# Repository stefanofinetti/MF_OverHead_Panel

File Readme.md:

# Overhead Panel

A compact Airbus A319/320/321 overhead panel for MobiFlight: 3D-printed
panels and Korry-style push buttons, the boards that carry every switch,
light and display, and the firmware for its three OLED displays.

The panel covers **ADIRS**, **AIR COND**, **ANTI ICE**, **APU**, **ELEC**,
**EXT LT**, **FUEL**, **GPWS** and **SIGNS**.

## v2 in short

v1 is one four-layer board, 313 × 206 mm, behind the whole panel. It works,
but it costs well over €100 once shipping and customs are added, and a
single mistake means reordering all of it.

v2 follows the printed panels instead: **eight small section boards, one
under each panel, and a 137 × 89 mm mainboard on the floor of the case**,
joined by ribbon cables. All nine are two-layer, 1.6 mm boards.

* **The printed parts do not change.** Panels, frames, Korry buttons and
  cases are the same. Only the floor of the lower-left case part is
  reprinted, with four bosses for the mainboard.
* **The section boards are cut out of the v1 layout.** Every switch, LED
  and hole stays at its v1 position, so each panel screws down exactly as
  before.
* **The pin map does not change.** Every switch is on the same ATmega pin
  and every annunciator on the same bit of the same shift-register chain,
  so the module config and the MobiFlight project stay valid. A few
  additions are listed under [Moving from v1](#moving-from-v1).

**Status (September 2026):** all nine boards are drawn and routed. ERC,
DRC and schematic parity are clean, and every ribbon and backlight pin was
checked against the board at the other end. **Nothing has been ordered or
built yet.** The firmware v2 needs is in `SF_OVHD` 1.2.0. The reprinted
case floor is still to do. v1 is the board that has been built and tested. It is
kept in `Kicad Files/` as the reference the v2 boards were cut from, **not
to be built**: build v2.

## What is in the repository

| Folder | What it holds |
|---|---|
| `Mainboard/` | The v2 mainboard: KiCad project, schematic (a root sheet and six sub-sheets) and routed PCB. See [its readme](Mainboard/README.md) |
| `Section_ADIRS/` … `Section_SIGNS/` | The eight v2 section boards, one KiCad project each, with a readme apiece |
| `Libraries/` | Parts shared by every v2 board: `OVHD.pretty` (Korry, toggle, ADR rotary, annunciator LED), `OVHD.kicad_sym`, and `3dmodels/` |
| `docs/board-split.md` | The v2 design document: decisions, power, annunciator currents, the ribbon pinouts, and why each choice was made |
| `SF_OVHD/` | The MobiFlight firmware and the installable Community package, with the module config for the panel. See [its readme](SF_OVHD/README.md) |
| `STL Files/` | Everything to print: one STL per filament colour for each panel, a ready `.3mf` for multi-colour printers, the Korry buttons and cases, the four case parts, the frames and the support |
| `STL Files/FaceDown_Printing/` | The APU panel redesigned to print face down. The other panels will follow |
| `STL Files/Levers/` | The exterior light levers and the paddle knobs |
| `3D Files/` | The SketchUp sources for the panel, the Korry buttons and the support |
| `Kicad Files/` | **v1**, for reference only: the single big board, as sent to JLCPCB on 3 March 2025. Do not build it |

`OverheadPanel.zip` is an older snapshot of `Kicad Files/` from January
2025, kept for reference.

## The boards

```
                        ┌─ ribbon ──► 8 section boards (switches, annunciators, backlight LEDs)
 9 V jack ─► mainboard ─┤
 USB-B    ─►            └─ 2 wires ─► 8 section boards (backlight, 9 V)
```

The mainboard carries every active part. The section boards carry only
their switches, LEDs and resistors, and the OLED sockets.

| Board | PCB (mm) | Switches | Annunciators | Backlight LEDs | Ribbon → mainboard | Backlight → mainboard |
|---|---|---|---|---|---|---|
| [ADIRS](Section_ADIRS/README.md) | 132.5 × 81.5 | 3 ADR rotaries, GND CTL | 1 | 18 | 20 pins → J701 | J601 |
| [FUEL](Section_FUEL/README.md) | 177.5 × 40 | 7 Korry | 14 | 14 | 26 pins → J702 | J602 |
| [ELEC](Section_ELEC/README.md) | 177.5 × 39.5 | 3 Korry | 5 | 10 | 20 pins → J703 | J603 |
| [GPWS](Section_GPWS/README.md) | 159.5 × 39 | 4 Korry | 6 | 9 | 14 pins → J704 | J604 |
| [AIR COND](Section_AIRCOND/README.md) | 150.5 × 39 | 4 Korry | 8 | 13 | 16 pins → J705 | J605 |
| [EXT LT](Section_EXTLT/README.md) | 159.5 × 79.5 | 8 toggles | — | 31 | 14 pins → J706 | J606 |
| [APU](Section_APU/README.md) | 39 × 79.5 | 2 Korry | 4 | 5 | 10 pins → J707 | J607 |
| [SIGNS](Section_SIGNS/README.md) | 108.5 × 79.5 | 3 Korry, 3 toggles | 6 | 22 | 16 pins → J708 | J608 |
| **Total** | | **49 inputs** | **44** | **122** | | |

The three OLEDs (BATT 1, BATT 2 on ELEC, ADIRS on ADIRS) plug into sockets
on their section boards, as on v1, and reach the mainboard through the
ribbon.

### The mainboard

137 × 89 mm, two layers, GND poured on both. The chips and connectors are on
top, and the small 1206 parts of the dense groups are underneath their chip.

* **Microcontroller:** ATmega2560 with a CH340G for USB. MobiFlight sees it
  as a Mega.
* **Power:** 9 V in through reverse protection, a TVS and a 470 µF bulk
  capacitor, then two resettable fuses, one for the backlight and one for
  the MIC29302 5 V regulator. A TPS2115A feeds the logic from that 5 V, or
  from USB when the 9 V is off. An AMS1117 makes 3.3 V for the PCA9548A
  and the OLEDs.
* **Annunciators:** four TI TLC5927 constant-current sinks, one per legend
  colour, in the two v1 chains (`ANN_LOWER`, `ANN_UPPER`). Each has a fixed
  1 kΩ on `R-EXT`, about 19 mA per LED. The trimmers of v1 are gone.
* **Three switches driven by the firmware:**
  * **D44:** backlight dimmer, an IRLIZ44N on the common return of the
    eight backlight branches;
  * **D45:** annunciator dimmer, on the LED anode rail;
  * **D46:** power to the four TLC5927, so they start clean however the
    9 V was plugged in.

  D44 and D45 undriven means dark.
* **Displays:** a PCA9548A I2C multiplexer at 0x71, channels 0–2 for
  BATT 1, BATT 2 and ADIRS.

### The section boards

* Every v1 part stays at its v1 coordinates. The new parts go on the
  **back**: the shrouded IDC header, the JST PH backlight connector and the
  few new resistors. Nothing new stands proud of the front.
* No ICs. The annunciator LEDs have no resistors, because the TLC5927 is a
  current sink.
* Backlight strings of two LEDs on 150 Ω, at 17 mA. Where the split leaves
  one LED alone (GPWS, AIR COND, EXT LT, APU), it gets 330 Ω for the same
  current.
* Each board sits in the middle of its A4 sheet. Its grid origin is set to
  where v1's (0, 0) lies, so KiCad shows v1 coordinates. The offset is in
  the title block.

## Building one

1. **Print** the panels, buttons, cases and frames from `STL Files/`.
2. **Reprint the floor of the lower-left case part** with four bosses and M3
   heat-set inserts for the mainboard. The mainboard's M3 holes are 4 mm in
   from its corners. The floor is free over 141 × 93.5 mm between the
   pillars. The reprinted floor is not drawn yet.
3. **Order the boards.** Run the Fabrication Toolkit plugin in each of the
   nine projects to make the Gerbers, BOM and positions. No v2 production
   files have been generated yet.
4. **Assemble.** Everything is sized for hand soldering: 1206 passives,
   7 × 5 mm crystals, generous spacing. Values, polarity, pin 1 and `K`
   marks are on the silkscreen of the side each part is on, so no
   schematic is needed at the bench. The per-board readmes list what to
   watch for.
5. **Cable it:**
   * one straight IDC ribbon per board, pin 1 to pin 1, from J1 on the
     section board to its J70x;
   * one pair of 22–24 AWG wires per board, from J2 (JST PH, `+` and `−` on
     the silkscreen) to its J60x screw terminal, pin 1 `+`;
   * the 9 V from a panel-mount 5.5 × 2.1 jack to J101 (pin 1 `+`);
   * USB through a panel-mount USB-B extension to P201.
6. **Burn the bootloader.** A new ATmega2560 is blank. J201 is an in-line
   ISP header: 1 VCC, 2 RESET, 3 MISO, 4 MOSI, 5 SCK, 6 GND. With JP201 on
   2–3, the programmer powers the MCU alone. Burn the Arduino Mega
   bootloader once, then put JP201 back on 1–2. From then on, the board is
   flashed over USB like a Mega.
7. **Install the firmware and the module config**, as described in
   [the firmware readme](SF_OVHD/README.md), then bind the switches and
   lights in your MobiFlight project.

A 9 V / 3 A adapter is enough. The backlight takes about 1.1 A, and a light
test with all 44 annunciators lit adds about 1 A.

## Moving from v1

The pin map is the same, so the v1 module config and project keep working,
with these changes:

* **Flash `SF_OVHD` 1.2.0 or later.** Its custom device powers the TLC5927
  up through D46 once the board has started. With older or stock MobiFlight
  firmware the annunciators stay dark on v2.
* **Load the module config from the 1.2.0 package.** It adds two PWM outputs,
  `BL_PWM` on D44 (backlight) and `ANN_PWM` on D45 (annunciators). D46 is not
  in it, because the custom device owns it.
* **Two new rows in the MobiFlight project** to drive them, typically INTEG
  LT for D44 and ANN LT BRT/DIM for D45. At 0, or with the Connector
  closed, the backlight and the annunciators are dark.
* **NO SMOKING:** v1 read it on the toggle's other contact, and the
  MobiFlight row was inverted to make up for it. v2 reads it like every
  other toggle, so **remove the inversion** on that row.

## Known issues

* **The ADIRS panel labels its rotaries in the wrong order.** The printed
  panel reads ADR 1, ADR 2, ADR 3 from left to right. On the A320 the order
  is IR 1, IR 3, IR 2, and that is how the board is wired, on v1 and v2
  alike: the middle rotary is IR 3 and the right one is IR 2. The `.mfmc`
  follows the board. Only the printed labels are wrong, so read the middle
  knob as 3 and the right one as 2 until the panel is reprinted.

## Software

* [KiCad](https://www.kicad.org/) 10, for the v2 boards. The files are
  saved by KiCad 10 and do not open in older versions
* [Freerouting](https://github.com/freerouting/freerouting), only to
  reroute a board
* [SketchUp](https://www.sketchup.com), to change the printed parts
* [VS Code](https://code.visualstudio.com/) with
  [PlatformIO](https://platformio.org/), to build the firmware
* [MobiFlight](https://www.mobiflight.com/)

```bash
git clone https://github.com/stefanofinetti/MF_OverHead_Panel.git
```

## License

This code and all the items are released under the GPLv3.0 license. Feel free
to use them as you wish, as long as you redistribute the source code.
A mention would be nice, though, if you use this work: I invested a good
many hours in it, just for the amazing MobiFlight community.

## Acknowledgements

This project couldn't have seen the light without the excellent work, and
kind support, of [GaGagu](https://github.com/gagagu) and
[ElRal](https://github.com/elral). Their work is amazing, so please have a
look at their repositories.

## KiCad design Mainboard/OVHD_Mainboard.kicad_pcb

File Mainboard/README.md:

# OVHD Mainboard (v2)

The v2 mainboard: the microcontroller, power, annunciator drivers and
display multiplexer for the whole overhead. It sits on the floor of the
lower-left case part and reaches the eight section boards through ribbons
and backlight wires. The reasoning behind every choice is in
[`docs/board-split.md`](../docs/board-split.md).

* **PCB:** 137 × 89 mm, 2 layers, 1.6 mm, GND poured on both sides.
* **Fixing:** four M3 holes, 4 mm in from the corners, for bosses with
  heat-set inserts in the reprinted case floor.
* **Parts:** 123. 65 of them are on the bottom.
* **Status:** routed with Freerouting. ERC, DRC (every warning on) and
  schematic parity are clean. Not yet ordered.

**Top**, with the chips and connectors:

**Bottom**, with the small 1206 parts under their chips:

Rendered by KiCad from the board file. The bottom is seen from below, so it
is mirrored against the top.

## Schematic

| Sheet | What is on it |
|---|---|
| `power.kicad_sch` | 9 V in, reverse diode, TVS, bulk capacitor, the two fuses, MIC29302 (5 V) |
| `usb_supply.kicad_sch` | USB-B, CH340G, TPS2115A supply selector, AMS1117 (3.3 V), ISP header, JP201 |
| `mcu.kicad_sch` | ATmega2560, 16 MHz crystal, reset, decoupling |
| `i2c.kicad_sch` | PCA9548A, address switch, pull-ups |
| `annunciators.kicad_sch` | The four TLC5927, the anode dimmer (D45) and the TLC5927 supply switch (D46) |
| `connectors.kicad_sch` | The eight ribbon headers, the eight backlight terminals, the backlight dimmer (D44) |

Local libraries: `TLC5927.kicad_sym` / `TLC5927.pretty` and
`TPS2115A.kicad_sym`. Every part has a description field that says why it
is there and, where it replaces a v1 part, which one.

## Connectors and settings

| Ref | What | Notes |
|---|---|---|
| J101 | 9 V in, 5.08 mm screw terminal | From the panel-mount 5.5 × 2.1 jack. Pin 1 `+` |
| P201 | USB-B | To the panel-mount USB-B extension |
| J201 | ISP header, 1 × 6 | 1 VCC, 2 RESET, 3 MISO, 4 MOSI, 5 SCK, 6 GND |
| JP201 | Power selector | 1–2: MCU from the board's 5 V (normal use). 2–3: MCU from J201's VCC only, to burn the bootloader |
| SW401 | PCA9548A address | All off = 0x70. **Set A0 on: the board runs at 0x71**, which `SF_OVHD` expects |
| J701–J708 | Ribbons to ADIRS, FUEL, ELEC, GPWS, AIR COND, EXT LT, APU, SIGNS | Shrouded, keyed. Straight ribbon, pin 1 to pin 1. Each is labelled on the silkscreen with its board |
| J601–J608 | Backlight to the same eight boards, in the same order | 3.5 mm screw terminals. Pin 1 `+9V_BL`, pin 2 the switched return |

The pinout of every ribbon is in the design document, under *Ribbon
pinouts*.

## Annunciator drivers

| Ref | Colour | Chain and bits | v1 ref |
|---|---|---|---|
| U501 | white | `ANN_LOWER` 0–15 | U6 |
| U502 | blue | `ANN_LOWER` 16–31 | U7 |
| U503 | amber | `ANN_UPPER` 0–15 | U8 |
| U504 | green and amber | `ANN_UPPER` 16–31 | U5 |

`ANN_LOWER` has its latch on D23, clock on D24 and data on D22. `ANN_UPPER`
has its latch on D27, clock on D26 and data on D25, as on v1.

* **`R-EXT` is a fixed 1 kΩ (R501–R504):** I = 1.25 V / R × 15 ≈ 19 mA
  per LED. If you ever change it, stay between ~160 Ω and ~1.9 kΩ, the
  chip's range at power-up.
* **Nothing else on `R-EXT`,** above all no capacitor. On the v1 board a
  100 nF there made the chips drop their outputs as soon as two or three
  were on together. See the design document.
* **`OE` is tied hard to GND.** On the TLC5927 it is also the mode pin, so
  it must never get PWM.
* **1 kΩ in series on CLK, LE and SDI (R511–R520),** at the chips' end.

## Pins the firmware drives

| Pin | Drives | Undriven or low |
|---|---|---|
| D44 | Q601 (IRLIZ44N), the common return of the backlight | backlight off |
| D45 | Q501/Q502, the annunciator anode rail `+5V_LED` | annunciators dark |
| D46 | Q503/Q504, the TLC5927 supply | TLC5927 unpowered |

D44 and D45 are plain MobiFlight PWM outputs, `BL_PWM` and `ANN_PWM` in the
`.mfmc`. D46 belongs to the `SF_OVHD` custom device, from firmware 1.2.0. It
powers the chips up after the board has started, and again on message 5. See
[the firmware readme](../SF_OVHD/README.md#annunciator-power-up-d46).

## Assembly notes

* **Bottom side:** the 1206 parts of the dense groups, each under its chip:
  * the MCU and CH340G decoupling and crystal parts;
  * the I2C pull-ups;
  * the TLC5927 `R-EXT` resistors, VDD capacitors and series resistors;
  * the resistors of the three MOSFET switches;
  * the MIC29302 feedback divider and capacitors.

  Solder the bottom side first, then the top.
* **Q601** lies flat on its isolated tab. At ~1.1 A it needs no heatsink.
* **The polarity marks are on the silkscreen:** the electrolytics, the `K` at D101
  and at the power LED D201, and `+` and `−` at J101 and at every
  backlight terminal. D102 (SMBJ12CA) is bidirectional: it fits either way round.
* **Before flashing any firmware,** burn the bootloader through
  J201 with JP201 on 2–3, then move JP201 back to 1–2.

## Design rules

| Net class | Track | Clearance | Nets |
|---|---|---|---|
| HiCurrent | 0.8 mm | 0.3 mm | `VIN_RAW`, `+9V`, `+9V_BL`, `BL_RET` |
| Power | 0.5 mm | 0.25 mm | `+9V_REG`, `+5V_LED` |
| PowerNarrow | 0.35 mm | 0.2 mm | `5V_EXT`, `VBUS`, the widest that enters the TPS2115A's 0.65 mm pins |
| Default | 0.25 mm | 0.2 mm | everything else |

The minimum track is 0.15 mm, for a few escapes between TQFP and SOIC pins,
within JLCPCB's 0.127 mm.

## Mechanical

* The board is drawn in v1 coordinates, at x 32–169, y 134.5–223.5, under
  EXT LT and the lower edge of GPWS. That way it can be checked against the
  section boards above it.
* EXT LT's J1 and J2 hang over the TLC5927 block, where nothing is taller
  than a SOIC. No ribbon header sits under another board's connector.
* With today's case there are 27 mm from the floor to the underside of the
  section boards. The reprinted floor is meant to raise that to 30–35 mm.

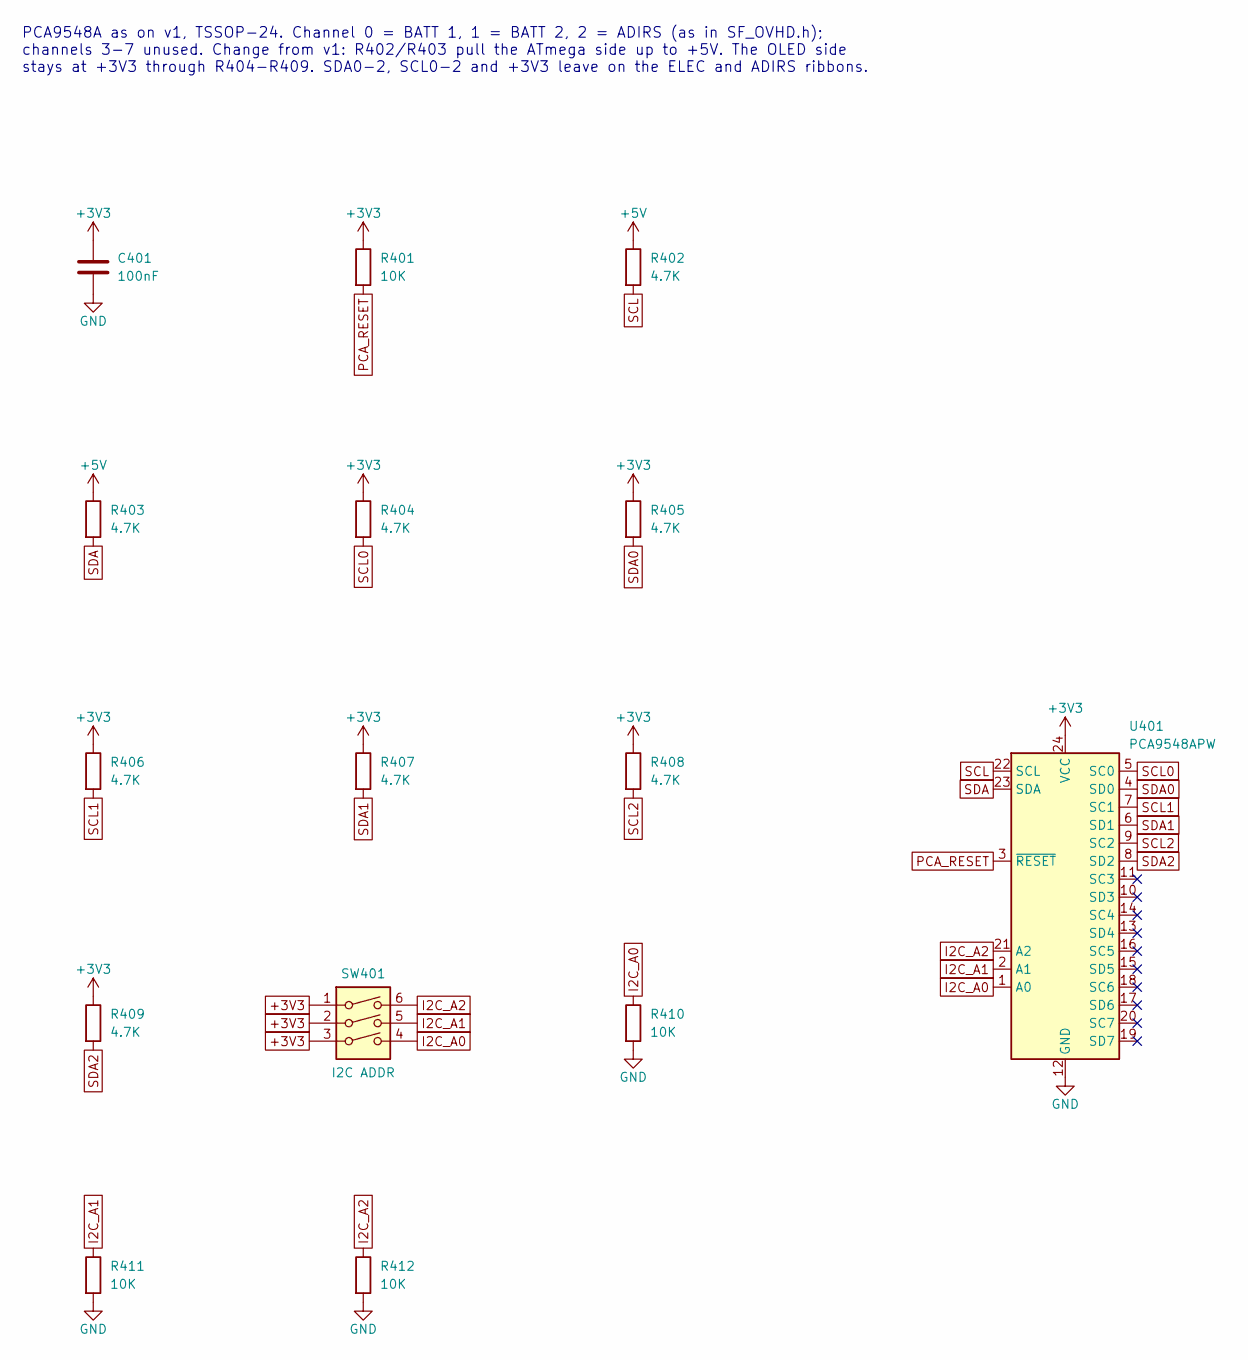
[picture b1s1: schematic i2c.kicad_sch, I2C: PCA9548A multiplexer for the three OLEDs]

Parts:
C401: 100nF; C_1206_3216Metric_Pad1.33x1.80mm_HandSolder
R401, R410, R411, R412: 10K; R_1206_3216Metric_Pad1.30x1.75mm_HandSolder
R402, R403, R404, R405, R406, R407, R408, R409: 4.7K; R_1206_3216Metric_Pad1.30x1.75mm_HandSolder
SW401: I2C ADDR; SW_DIP_SPSTx03_Slide_9.78x9.8mm_W7.62mm_P2.54mm
U401: PCA9548APW; TSSOP-24_4.4x7.8mm_P0.65mm

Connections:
+3V3: C401.1, R401.1, R404.1, R405.1, R406.1, R407.1, R408.1, R409.1, SW401.1, SW401.2, SW401.3, U401.24 (VCC); also elsewhere on the board
+5V: R402.1, R403.1; also elsewhere on the board
GND: C401.2, R410.2, R411.2, R412.2, U401.12 (GND); also elsewhere on the board
I2C_A0: R410.1, SW401.4, U401.1 (A0)
I2C_A1: R411.1, SW401.5, U401.2 (A1)
I2C_A2: R412.1, SW401.6, U401.21 (A2)
PCA_RESET: R401.2, U401.3 (~RESET)
SCL: R402.2, U401.22 (SCL); also elsewhere on the board
SCL0: R404.2, U401.5 (SC0); also elsewhere on the board
SCL1: R406.2, U401.7 (SC1); also elsewhere on the board
SCL2: R408.2, U401.9 (SC2); also elsewhere on the board
SDA: R403.2, U401.23 (SDA); also elsewhere on the board
SDA0: R405.2, U401.4 (SD0); also elsewhere on the board
SDA1: R407.2, U401.6 (SD1); also elsewhere on the board
SDA2: R409.2, U401.8 (SD2); also elsewhere on the board

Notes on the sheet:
PCA9548A as on v1, TSSOP-24. Channel 0 = BATT 1, 1 = BATT 2, 2 = ADIRS (as in SF_OVHD.h); channels 3-7 unused. Change from v1: R402/R403 pull the ATmega side up to +5V. The OLED side stays at +3V3 through R404-R409. SDA0-2, SCL0-2 and +3V3 leave on the ELEC and ADIRS ribbons.

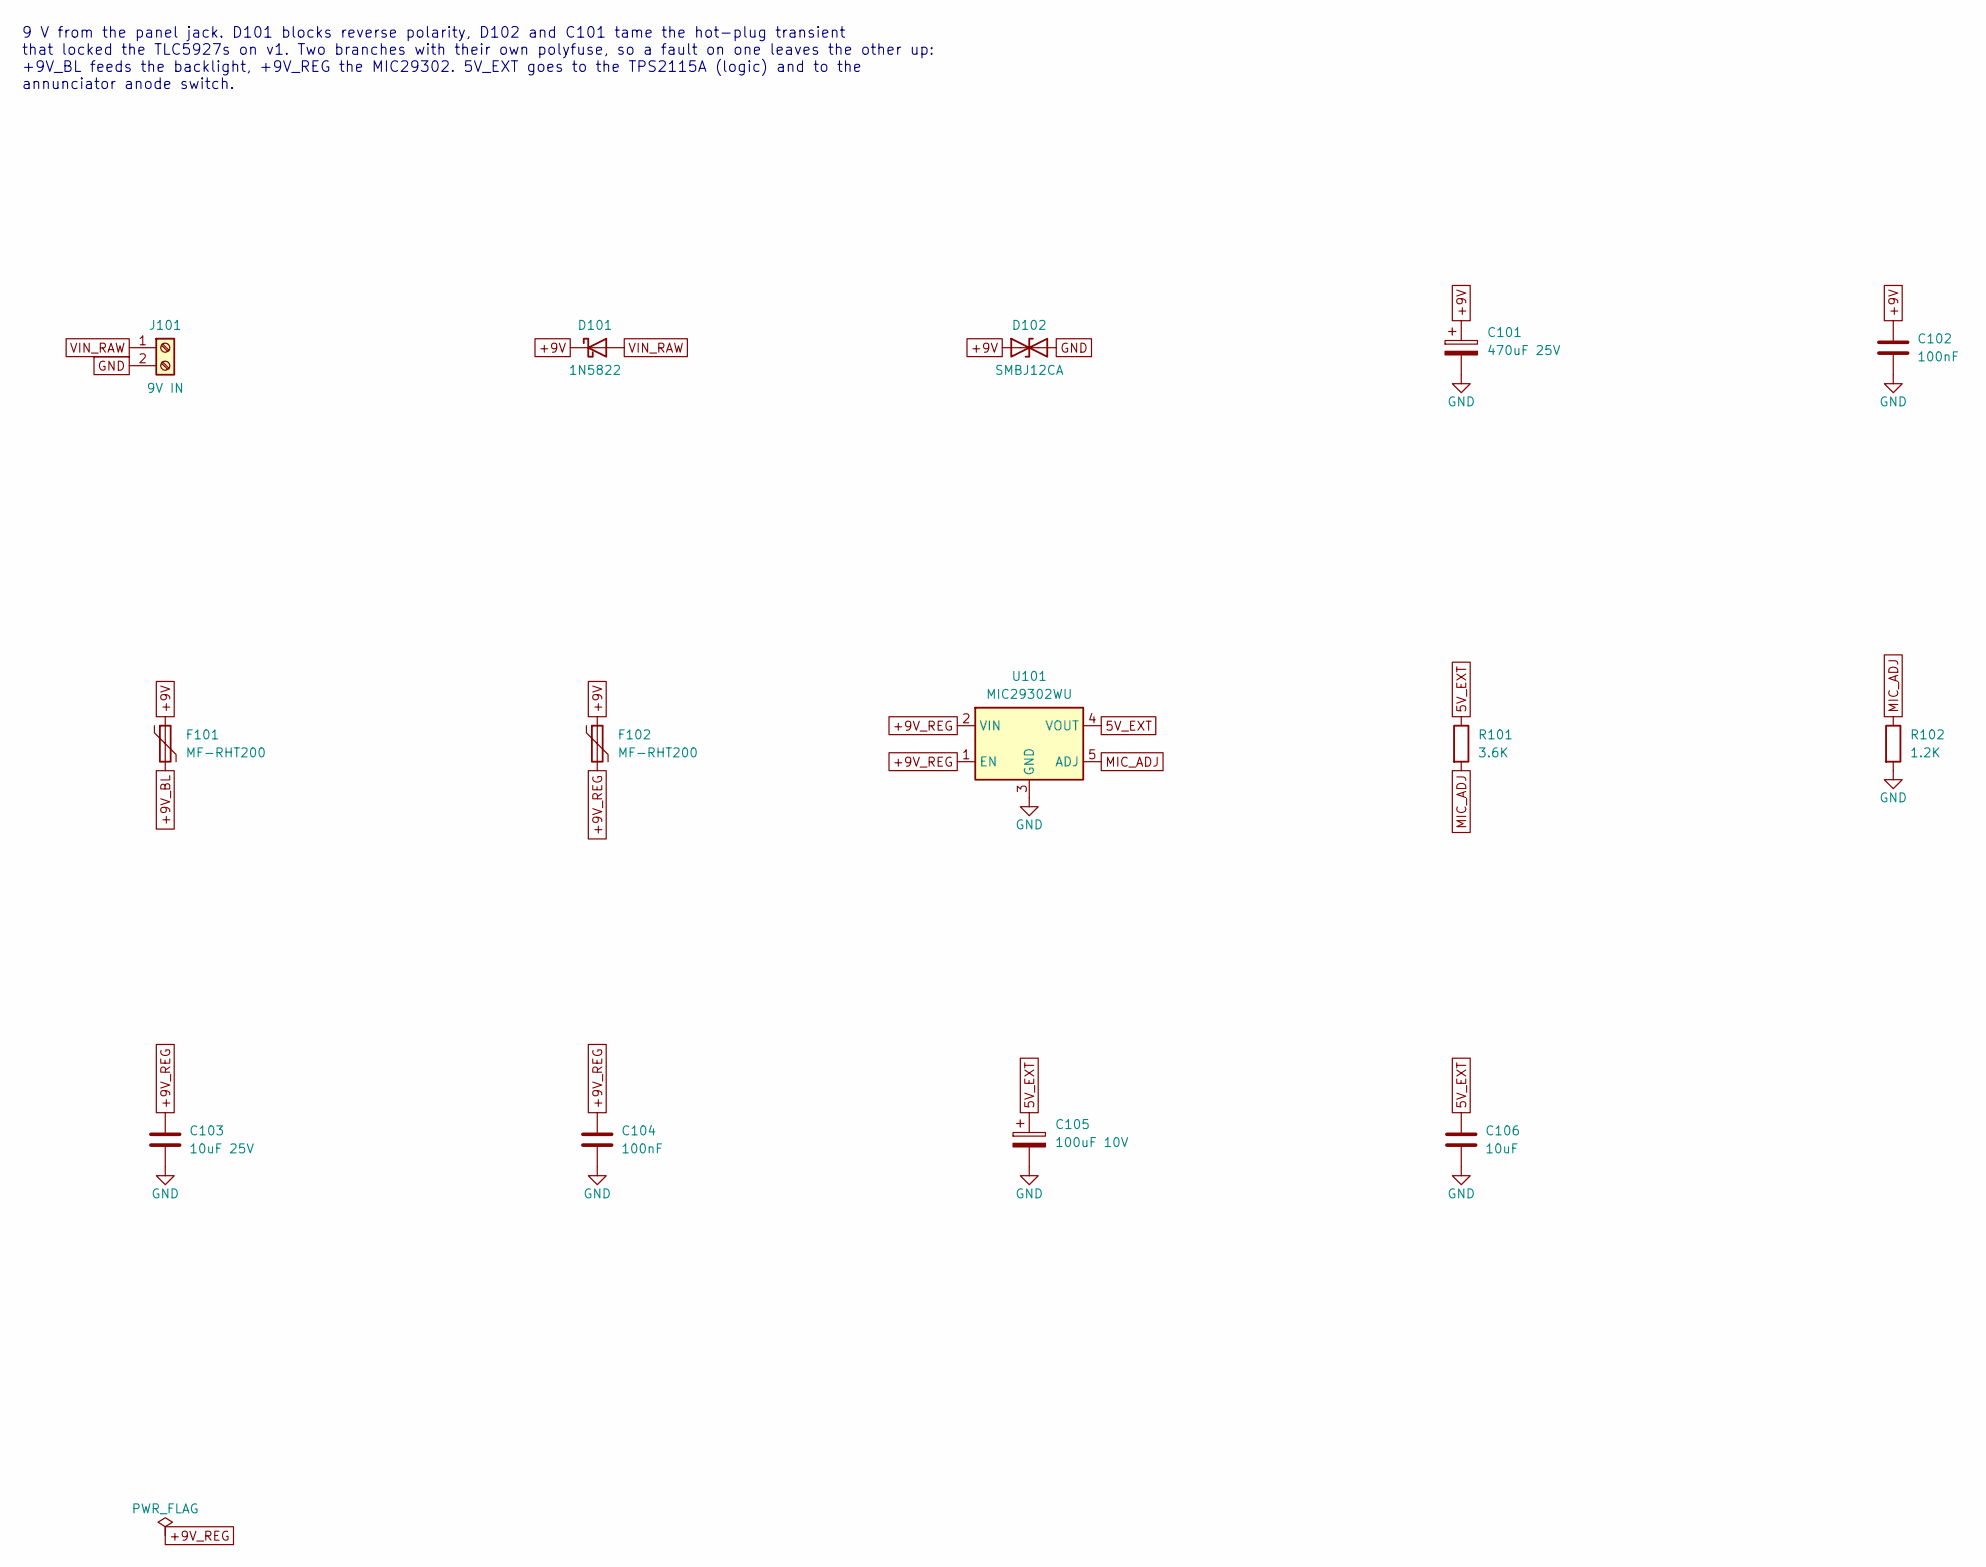
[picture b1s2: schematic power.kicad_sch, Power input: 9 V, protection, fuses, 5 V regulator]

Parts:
C101: 470uF 25V; CP_Radial_D10.0mm_P5.00mm
C102, C104: 100nF; C_1206_3216Metric_Pad1.33x1.80mm_HandSolder
C103: 10uF 25V; C_1206_3216Metric_Pad1.33x1.80mm_HandSolder
C105: 100uF 10V; CP_Radial_D6.3mm_P2.50mm
C106: 10uF; C_1206_3216Metric_Pad1.33x1.80mm_HandSolder
D101: 1N5822; D_DO-201AD_P15.24mm_Horizontal
D102: SMBJ12CA; D_SMB_Handsoldering
F101, F102: MF-RHT200; Fuse_Bourns_MF-RHT200
J101: 9V IN; TerminalBlock_Phoenix_MKDS-1,5-2-5.08_1x02_P5.08mm_Horizont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
R101: 3.6K; R_1206_3216Metric_Pad1.30x1.75mm_HandSolder
R102: 1.2K; R_1206_3216Metric_Pad1.30x1.75mm_HandSolder
U101: MIC29302WU; TO-263-5_TabPin3

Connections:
5V_EXT: C105.1, C106.1, R101.1, U101.4 (VOUT); also elsewhere on the board
+9V: C101.1, C102.1, D101.1 (K), D102.1 (A1), F101.1, F102.1
+9V_BL: F101.2; also elsewhere on the board
+9V_REG: C103.1, C104.1, F102.2, U101.1 (EN), U101.2 (VIN)
GND: C101.2, C102.2, C103.2, C104.2, C105.2, C106.2, D102.2 (A2), J101.2, R102.2, U101.3 (GND); also elsewhere on the board
MIC_ADJ: R101.2, R102.1, U101.5 (ADJ)
VIN_RAW: D101.2 (A), J101.1

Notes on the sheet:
9 V from the panel jack. D101 blocks reverse polarity, D102 and C101 tame the hot-plug transient that locked the TLC5927s on v1. Two branches with their own polyfuse, so a fault on one leaves the other up: +9V_BL feeds the backlight, +9V_REG the MIC29302. 5V_EXT goes to the TPS2115A (logic) and to 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

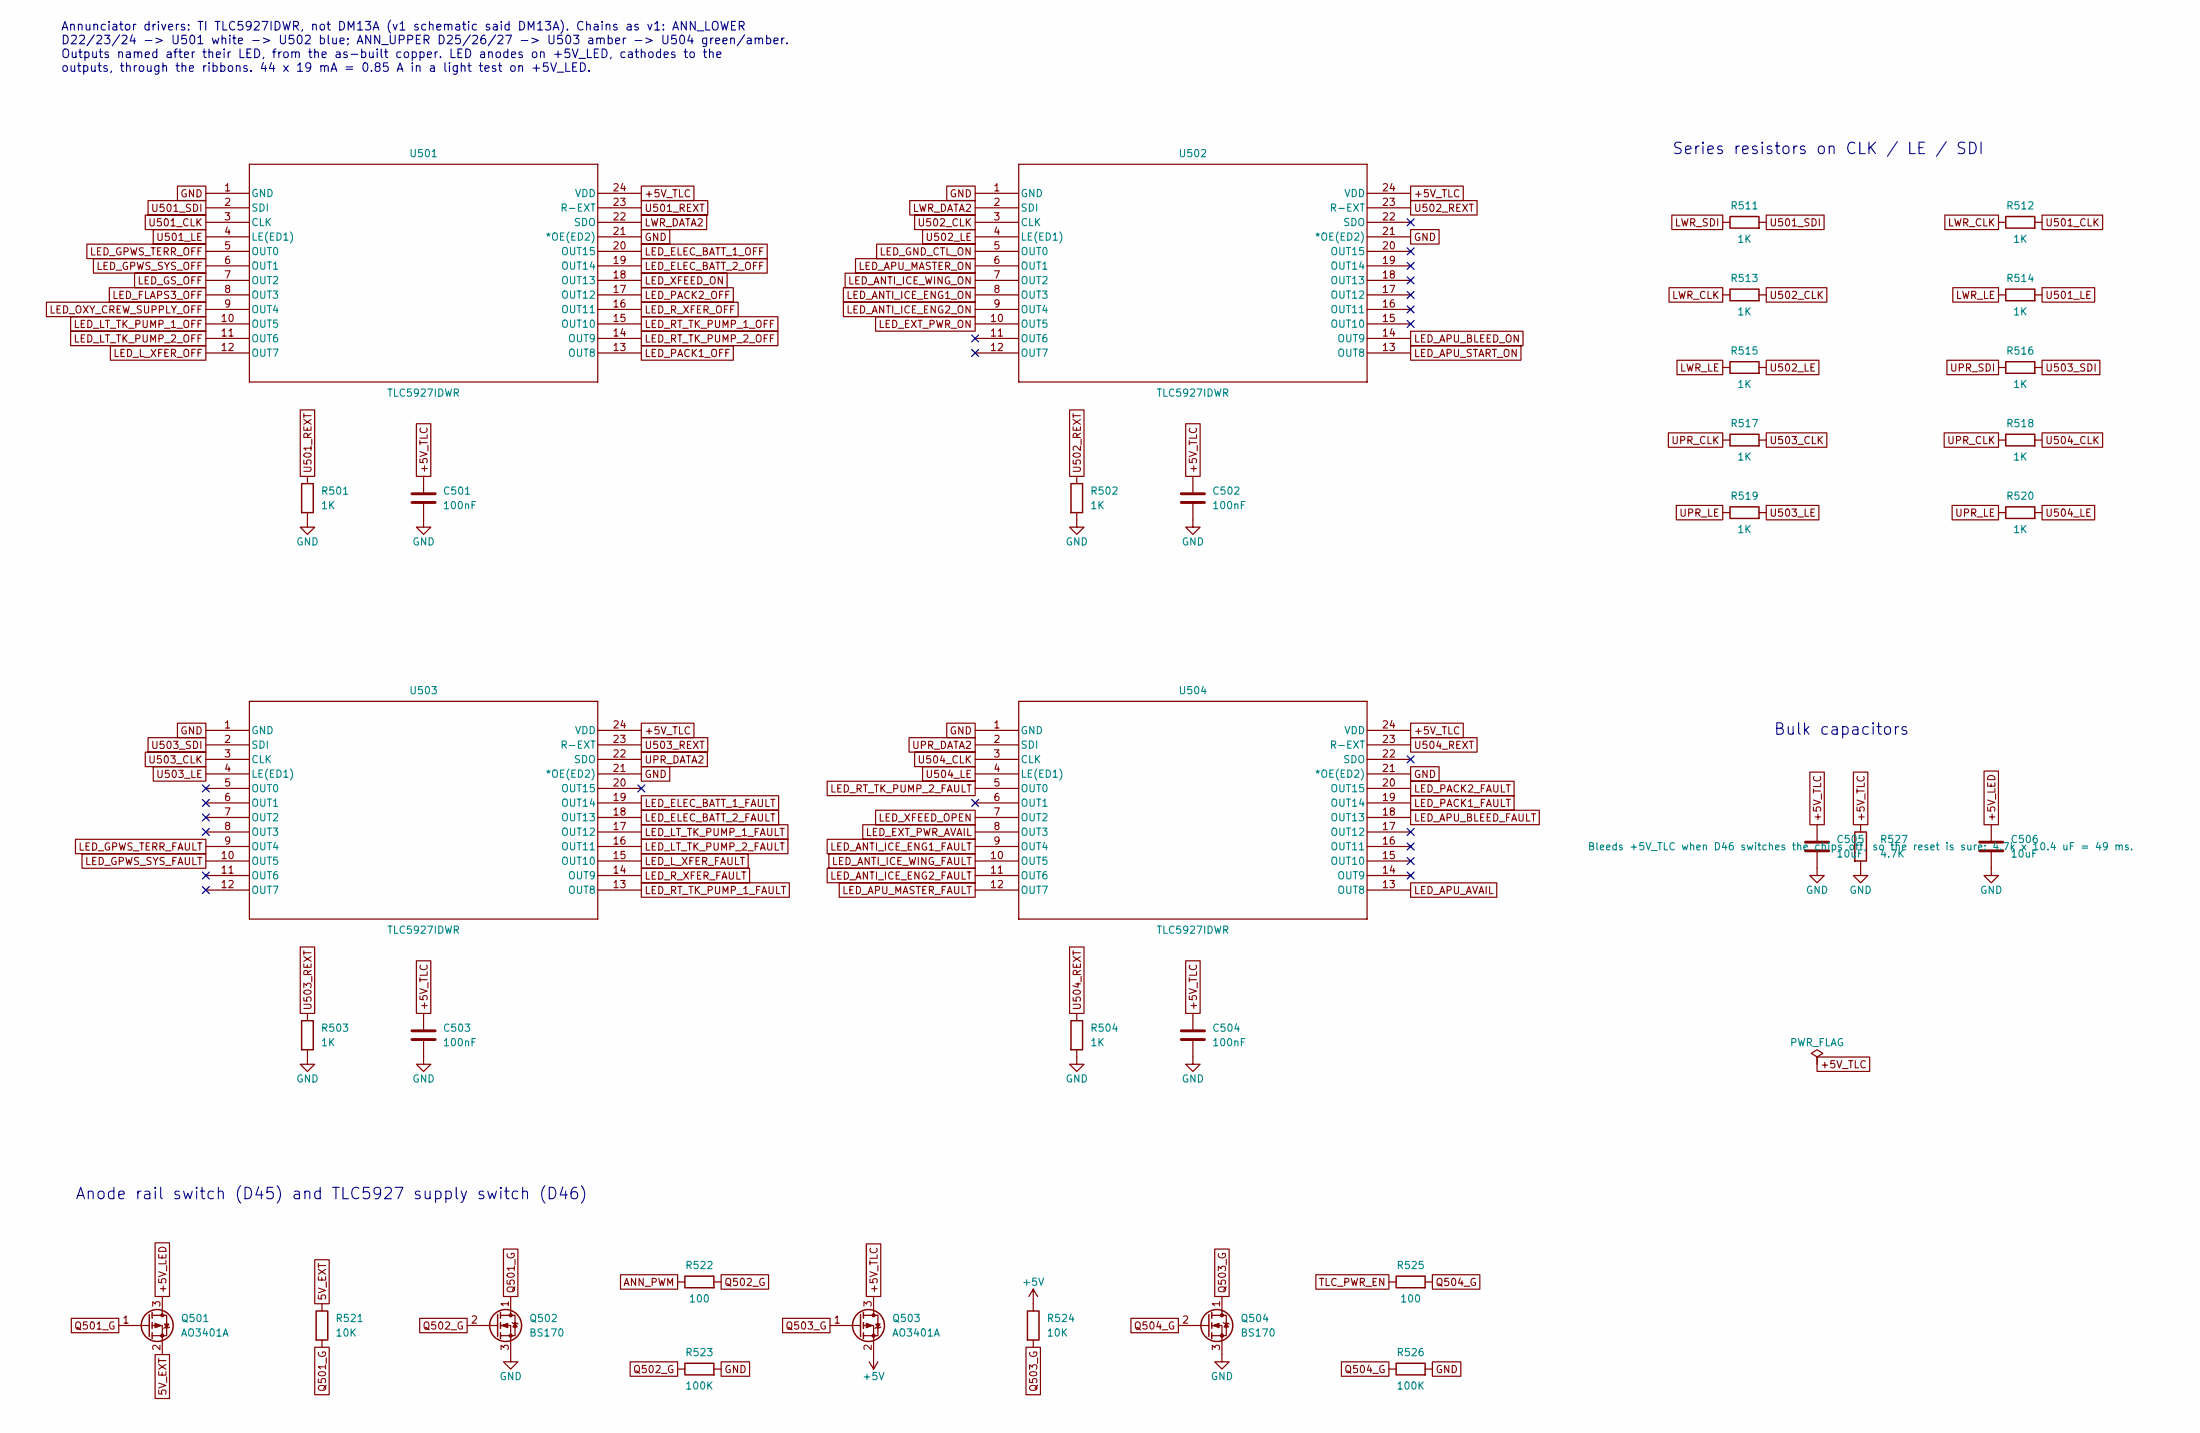
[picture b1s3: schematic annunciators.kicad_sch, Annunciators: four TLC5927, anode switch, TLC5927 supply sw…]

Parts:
C501, C502, C503, C504: 100nF; C_1206_3216Metric_Pad1.33x1.80mm_HandSolder
C505, C506: 10uF; C_1206_3216Metric_Pad1.33x1.80mm_HandSolder
Q501, Q503: AO3401A; SOT-23
Q502, Q504: BS170; TO-92_Inline
R501, R502, R503, R504, R511, R512, R513, R514, R515, R516, R517, R518, R519, R520: 1K; R_1206_3216Metric_Pad1.30x1.75mm_HandSolder
R521, R524: 10K; R_1206_3216Metric_Pad1.30x1.75mm_HandSolder
R522, R525: 100; R_1206_3216Metric_Pad1.30x1.75mm_HandSolder
R523, R526: 100K; R_1206_3216Metric_Pad1.30x1.75mm_HandSolder
R527: 4.7K; R_1206_3216Metric_Pad1.30x1.75mm_HandSolder
U501, U502, U503, U504: TLC5927IDWR; DW24-M

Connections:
5V_EXT: Q501.2 (S), R521.1; also elsewhere on the board
+5V: Q503.2 (S), R524.1; also elsewhere on the board
+5V_LED: C506.1, Q501.3 (D); also elsewhere on the board
+5V_TLC: C501.1, C502.1, C503.1, C504.1, C505.1, Q503.3 (D), R527.1, U501.24 (VDD), U502.24 (VDD), U503.24 (VDD), U504.24 (VDD)
ANN_PWM: R522.1; also elsewhere on the board
GND: C501.2, C502.2, C503.2, C504.2, C505.2, C506.2, Q502.3 (S), Q504.3 (S), R501.2, R502.2, R503.2, R504.2, R523.2, R526.2, R527.2, U501.1 (GND), U501.21 (*OE(ED2)), U502.1 (GND), U502.21 (*OE(ED2)), U503.1 (GND), U503.21 (*OE(ED2)), U504.1 (GND), U504.21 (*OE(ED2)); also elsewhere on the board
LED_ANTI_ICE_ENG1_FAULT: U504.9 (OUT4); also elsewhere on the board
LED_ANTI_ICE_ENG1_ON: U502.8 (OUT3); also elsewhere on the board
LED_ANTI_ICE_ENG2_FAULT: U504.11 (OUT6); also elsewhere on the board
LED_ANTI_ICE_ENG2_ON: U502.9 (OUT4); also elsewhere on the board
LED_ANTI_ICE_WING_FAULT: U504.10 (OUT5); also elsewhere on the board
LED_ANTI_ICE_WING_ON: U502.7 (OUT2); also elsewhere on the board
LED_APU_AVAIL: U504.13 (OUT8); also elsewhere on the board
LED_APU_BLEED_FAULT: U504.18 (OUT13); also elsewhere on the board
LED_APU_BLEED_ON: U502.14 (OUT9); also elsewhere on the board
LED_APU_MASTER_FAULT: U504.12 (OUT7); also elsewhere on the board
LED_APU_MASTER_ON: U502.6 (OUT1); also elsewhere on the board
LED_APU_START_ON: U502.13 (OUT8); also elsewhere on the board
LED_ELEC_BATT_1_FAULT: U503.19 (OUT14); also elsewhere on the board
LED_ELEC_BATT_1_OFF: U501.20 (OUT15); also elsewhere on the board
LED_ELEC_BATT_2_FAULT: U503.18 (OUT13); also elsewhere on the board
LED_ELEC_BATT_2_OFF: U501.19 (OUT14); also elsewhere on the board
LED_EXT_PWR_AVAIL: U504.8 (OUT3); also elsewhere on the board
LED_EXT_PWR_ON: U502.10 (OUT5); also elsewhere on the board
LED_FLAPS3_OFF: U501.8 (OUT3); also elsewhere on the board
LED_GND_CTL_ON: U502.5 (OUT0); also elsewhere on the board
LED_GPWS_SYS_FAULT: U503.10 (OUT5); also elsewhere on the board
LED_GPWS_SYS_OFF: U501.6 (OUT1); also elsewhere on the board
LED_GPWS_TERR_FAULT: U503.9 (OUT4); also elsewhere on the board
LED_GPWS_TERR_OFF: U501.5 (OUT0); also elsewhere on the board
LED_GS_OFF: U501.7 (OUT2); also elsewhere on the board
LED_LT_TK_PUMP_1_FAULT: U503.17 (OUT12); also elsewhere on the board
LED_LT_TK_PUMP_1_OFF: U501.10 (OUT5); also elsewhere on the board
LED_LT_TK_PUMP_2_FAULT: U503.16 (OUT11); also elsewhere on the board
LED_LT_TK_PUMP_2_OFF: U501.11 (OUT6); also elsewhere on the board
LED_L_XFER_FAULT: U503.15 (OUT10); also elsewhere on the board
LED_L_XFER_OFF: U501.12 (OUT7); also elsewhere on the board
LED_OXY_CREW_SUPPLY_OFF: U501.9 (OUT4); also elsewhere on the board
LED_PACK1_FAULT: U504.19 (OUT14); also elsewhere on the board
LED_PACK1_OFF: U501.13 (OUT8); also elsewhere on the board
LED_PACK2_FAULT: U504.20 (OUT15); also elsewhere on the board
LED_PACK2_OFF: U501.17 (OUT12); also elsewhere on the board
LED_RT_TK_PUMP_1_FAULT: U503.13 (OUT8); also elsewhere on the board
LED_RT_TK_PUMP_1_OFF: U501.15 (OUT10); also elsewhere on the board
LED_RT_TK_PUMP_2_FAULT: U504.5 (OUT0); also elsewhere on the board
LED_RT_TK_PUMP_2_OFF: U501.14 (OUT9); also elsewhere on the board
LED_R_XFER_FAULT: U503.14 (OUT9); also elsewhere on the board
LED_R_XFER_OFF: U501.16 (OUT11); also elsewhere on the board
LED_XFEED_ON: U501.18 (OUT13); also elsewhere on the board
LED_XFEED_OPEN: U504.7 (OUT2); also elsewhere on the board
LWR_CLK: R512.1, R513.1; also elsewhere on the board
LWR_DATA2: U501.22 (SDO), U502.2 (SDI)
LWR_LE: R514.1, R515.1; also elsewhere on the board
LWR_SDI: R511.1; also elsewhere on the board
Q501_G: Q501.1 (G), Q502.1 (D), R521.2
Q502_G: Q502.2 (G), R522.2, R523.1
Q503_G: Q503.1 (G), Q504.1 (D), R524.2
Q504_G: Q504.2 (G), R525.2, R526.1
TLC_PWR_EN: R525.1; also elsewhere on the board
U501_CLK: R512.2, U501.3 (CLK)
U501_LE: R514.2, U501.4 (LE(ED1))
U501_REXT: R501.1, U501.23 (R-EXT)
U501_SDI: R511.2, U501.2 (SDI)
U502_CLK: R513.2, U502.3 (CLK)
U502_LE: R515.2, U502.4 (LE(ED1))
U502_REXT: R502.1, U502.23 (R-EXT)
U503_CLK: R517.2, U503.3 (CLK)
U503_LE: R519.2, U503.4 (LE(ED1))
U503_REXT: R503.1, U503.23 (R-EXT)
U503_SDI: R516.2, U503.2 (SDI)
U504_CLK: R518.2, U504.3 (CLK)
U504_LE: R520.2, U504.4 (LE(ED1))
U504_REXT: R504.1, U504.23 (R-EXT)
UPR_CLK: R517.1, R518.1; also elsewhere on the board
UPR_DATA2: U503.22 (SDO), U504.2 (SDI)
UPR_LE: R519.1, R520.1; also elsewhere on the board
UPR_SDI: R516.1; also elsewhere on the board

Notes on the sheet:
Series resistors on CLK / LE / SDI
Anode rail switch (D45) and TLC5927 supply switch (D46)
Bulk capacitors
Annunciator drivers: TI TLC5927IDWR, not DM13A (v1 schematic said DM13A). Chains as v1: ANN_LOWER D22/23/24 -> U501 white -> U502 blue; ANN_UPPER D25/26/27 -> U503 amber -> U504 green/amber. Outputs named after their LED, from the as-built copper. LED anodes on +5V_LED, cathodes to the outputs, thr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
